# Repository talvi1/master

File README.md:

<h3>Road Roughness Measurement System</h3> 
<h4>Introduction</h4>
Road roughness data is expensive and painstaking to gather. A new approach minimizes the overall cost of such systems by building a low cost and modular system that can be used to take measurements of the road roughness and can be used to supplement the more expensive equipment to map all of the roadways. The system supports the measurement of road surface roughness where data is not currently being collected such as smaller rural municipalities roads and residential city roads. The measurement of road roughness along with images that provide visual reference are used to quantify road surface conditions. 

<h4>System Architecture</h4>

The system block diagram shows the architecture to capture, process and display the required. Three independent nodes are used to collect acceleration data from the road. Each node uses a 6-DoF MPU6050 accelerometer connected to a STM32 Cortex M3 microcontroller via I2C. The microcontroller processes the data and sends the data packets to a Xbee transmitter. The system operates in a star network topology using the IEEE 802.15.4 protocol to receive the frames from each node. The receiver is connected to the Raspberry Pi. The Raspberry Pi simultaneously receives position data from a GPS module and road images captured from the camera. The data is processed on the Raspberry Pi and sent to a server to be displayed on a website showing the worst quality roads on a map. 

<h4>Data Processing Pipeline</h4>

Raw acceleration data captured from the accelerometers needs to be processed in order to create a quantifiable measurment of road roughness. Accelerometer data is first passed through a DC blocking filter in order to remove the gravity bias from the measurements. A 10th order bandpass filter is used to remove noise from the measurments and data is then integrated to calculate velocity. An algorithm is then used to compute vertical displacement in m/m, which provides the required road roughness value.   

<h4>Image Processing Pipeline</h4>

Images are captured of the road surface in order to provide data regarding potholes and cracks in the road surface. 

Raw images are processed in order to provide an indication of the degradation of the road surface. The edge detection algorithm is used after passing the image through a gaussian blur filter. The edge is dilated and a convex hull algorithm is used to draw an approximate outline around the cracks or potholes in the road surface. The size of the convex polygon indicates the severity of the degradation in the road surface.    

<h4>Results</h4>

The data captured and processed from the system descibed above was display on a website to show the roughest parts of the roads in the city. 

<h6>Notes</h6>
<sup>See attached report and paper under the document folder to see further details regarding the software/hardware implementation, testing and challenges encountered.</sup>

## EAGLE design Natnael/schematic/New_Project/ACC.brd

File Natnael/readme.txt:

Natnael 

voltage regulator

https://www.digikey.ca/product-detail/en/PHR-2/455-1165-ND/608607/?itemSeq=284871182

https://www.digikey.ca/product-detail/en/B2B-PH-K-S(LF)(SN)/455-1704-ND/926611/?itemSeq=284871166

https://www.digikey.ca/product-detail/en/232/36-232-ND/303804/?itemSeq=284870675

https://www.digikey.ca/product-detail/en/EN22/N145-ND/704825/?itemSeq=284870583

https://www.ablic.com/en/doc/datasheet/voltage_regulator/S818_E.pdf

https://www.digikey.com/product-detail/en/ablic-u-s-a-inc/S-818A33AUC-BGNT2U/1662-2000-1-ND/6696434

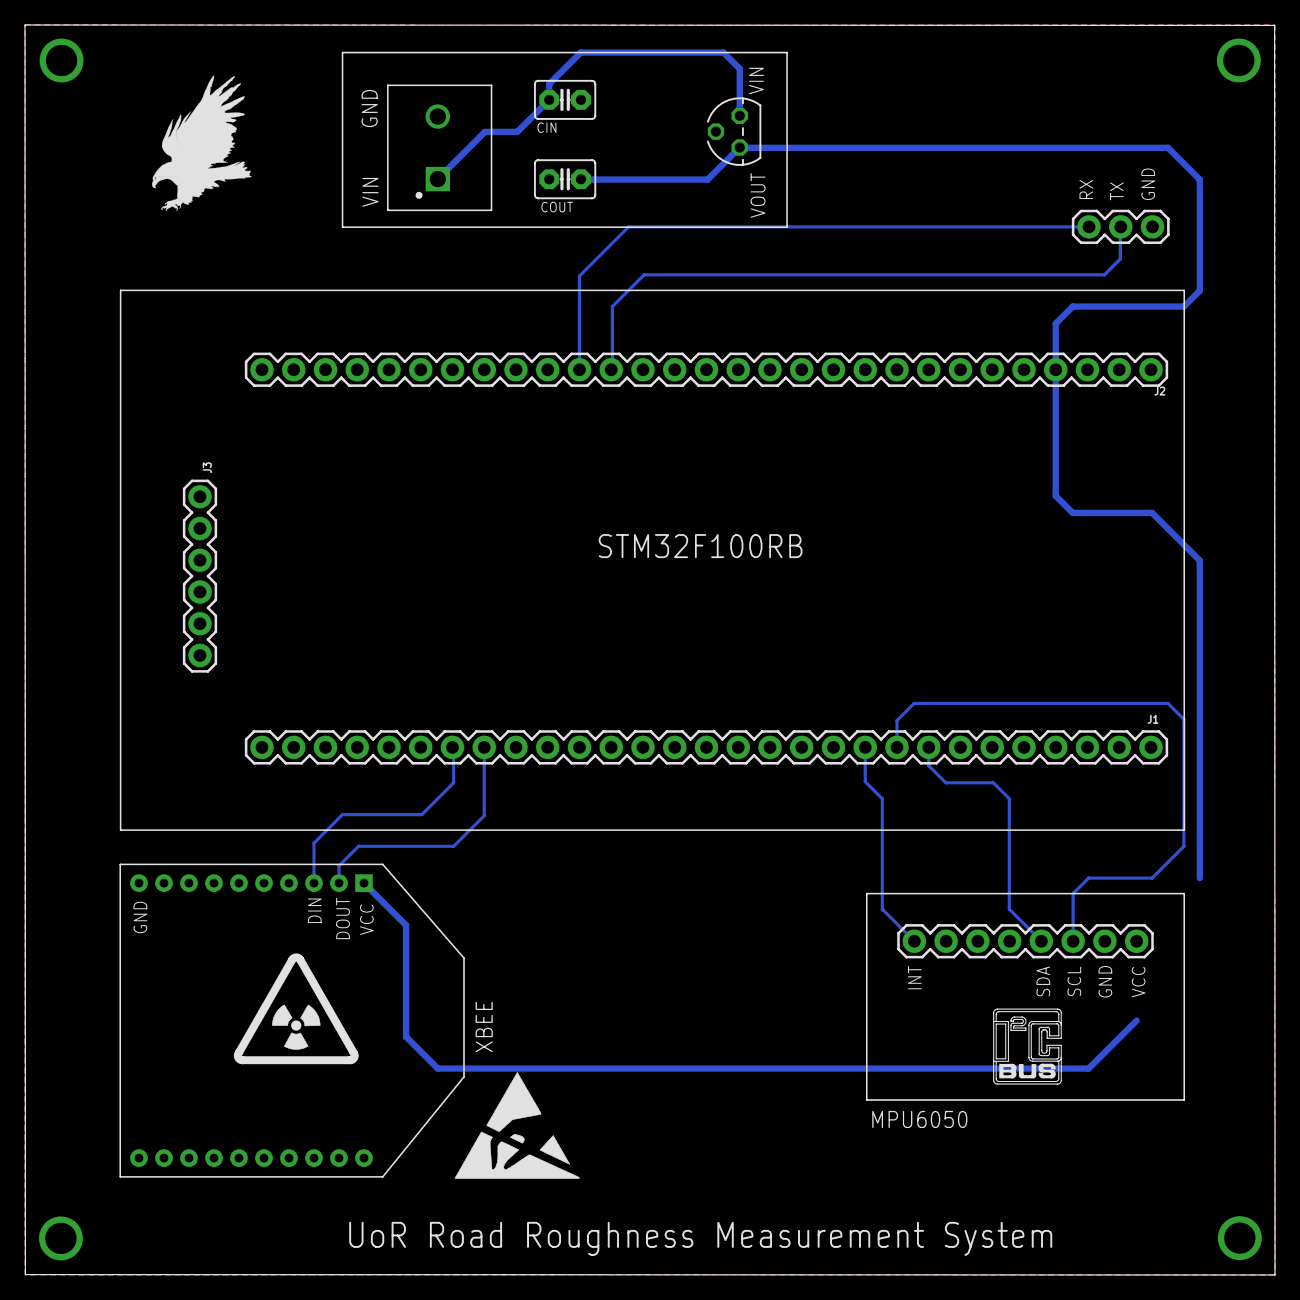
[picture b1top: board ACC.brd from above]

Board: 2 copper layers, 100.0 x 100.0 mm, 14 parts (0 on the bottom side), 10 nets.

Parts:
CIN: 1uF; C2.5-3
COUT: 2.2uF; C2.5-3
J1, J2: 1X29
J3: 1X06
J4: 1935161; PHOENIX_1935161
J5: 1X03
MPU6050: 1X08
U$2: EAGLE-PLC-8MM
U$3: ESD_10.00
U$5: I2C
U$6: RADIOACTIVE_10.00
VOLTAGE_REGULATOR: LP2950Z; TO92
XBEE: XBEE

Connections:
3V3: COUT.1, J2.4, VOLTAGE_REGULATOR.1
GND: CIN.2, COUT.2, J1.2, J1.29, J2.2, J2.29, J4.2, J5.1, MPU6050.7, VOLTAGE_REGULATOR.2, XBEE.10
PA2: J2.18, J5.2
PA3: J2.19, J5.3
PA9: J1.23, XBEE.3
PA10: J1.22, XBEE.2
PB5: J1.10, MPU6050.1
PB6: J1.9, MPU6050.6
PB7: J1.8, MPU6050.5
VIN: CIN.1, J4.1, VOLTAGE_REGULATOR.3

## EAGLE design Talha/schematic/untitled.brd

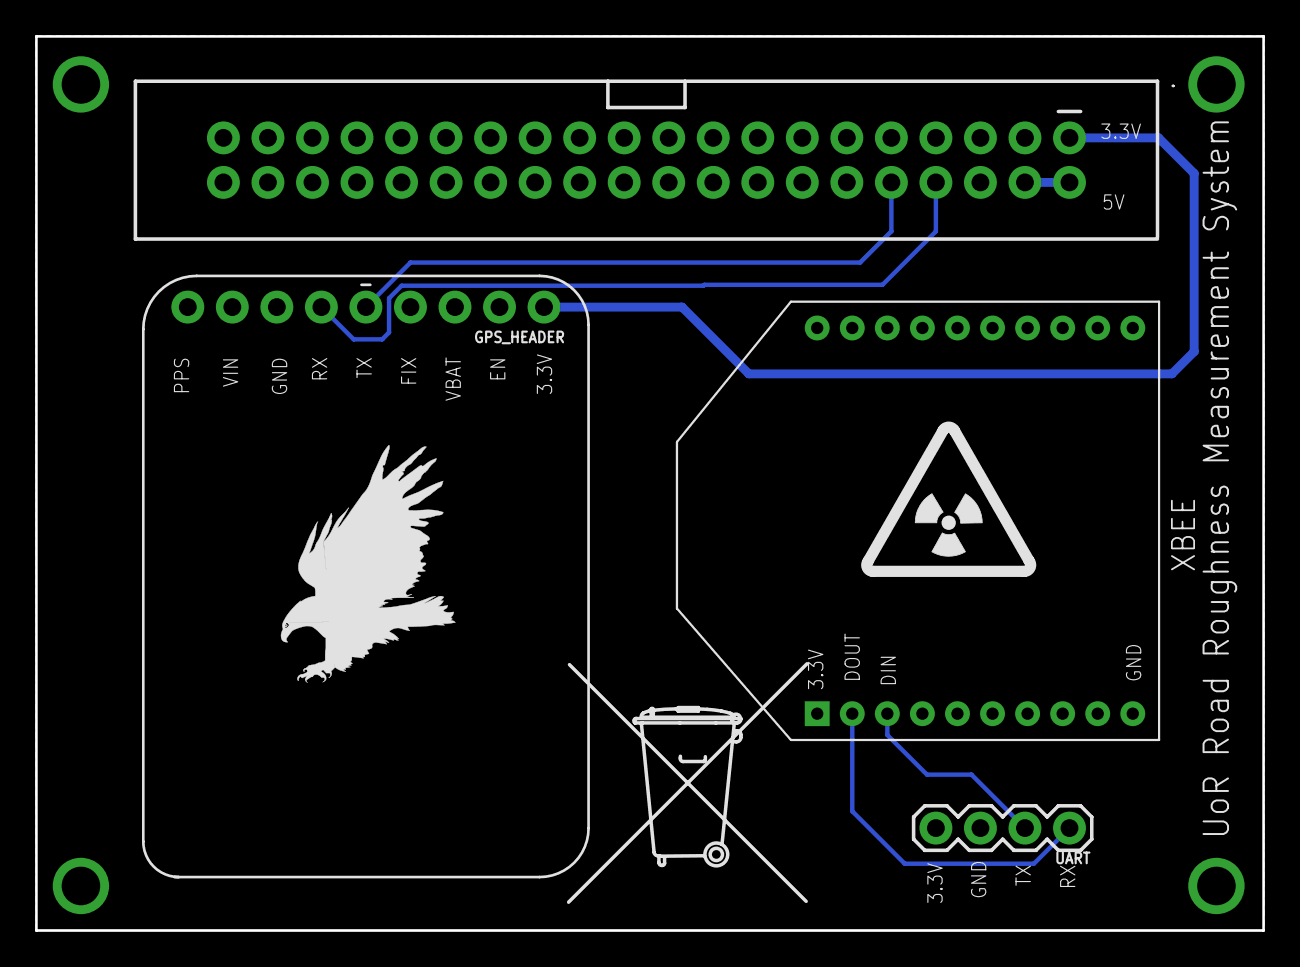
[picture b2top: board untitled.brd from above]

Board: 2 copper layers, 70.0 x 51.0 mm, 7 parts (0 on the bottom side), 8 nets.

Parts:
.: RASPBERRYPI-40-PIN-GPIO_PTH; 2X20_SHROUDED
GPS_HEADER: 1X09_NO_SILK
U$3: EAGLE-PLC-10MM
U$4: RADIOACTIVE_10.00
U$5: TONNE
UART: 1X04
XBEE: XBEE

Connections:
5V: ..2, ..4
GND: ..6, ..9, ..14, ..20, ..25, ..30, ..34, ..39, GPS_HEADER.7, UART.3, XBEE.10
unnamed: ..1, GPS_HEADER.1
unnamed: ..10, GPS_HEADER.5
unnamed: ..8, GPS_HEADER.6
RX: UART.1, XBEE.2
TX: UART.2, XBEE.3
VCC: ..17, XBEE.1

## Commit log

2018-09-24 test
2018-09-24 casdasdasd
2018-09-24 folder created
2018-11-29 test tala
2018-11-29 ACc and ADC test 1
2018-11-29 read me created
2018-11-29 read me for project
2018-12-02 initiall web push
2018-12-12 SPI example code
2019-01-10 updated acc driver
2019-01-11 testing for spi
2019-01-12 accelorometer test code
2019-01-12 more example code for stm32
2019-01-12 accel test code using i2c for mpu 6050
2019-01-13 accel test to produce float acceleration values
2019-01-13 initial push for raspberry pi code for camera, xbee, gps
2019-01-16 inital code push
2019-01-16 documentation for project device added
2019-01-20 i2c update
2019-01-20 readme file for natnael
2019-01-20 logs update
2019-01-20 logs removed
2019-01-20 logs re-added
2019-01-20 read me update
2019-01-20 python document created
2019-01-20 read me update 2
2019-01-21 updated regusters for MPU6050
2019-01-21 serial output formated for live plot
2019-01-23 Reference academic papers added & python csv code
2019-01-25 added reference paper on data processing
2019-01-25 Logs upload
2019-01-26 log 2
2019-01-26 added matlab scripts for filters and plotting data
2019-01-26 filter codes
2019-01-27 added testing plan
2019-01-28 xbee communication updated
2019-01-28 readme created
2019-01-30 update matlab scripts for filtering
2019-01-30 Updated testing plan
2019-01-31 testing plan updated and another reference paper added
2019-02-02 integration code for raspberry pi
2019-02-02 Battery/ Voltage regulator
2019-02-03 image processing script
2019-02-08 timer threads for camera
2019-02-08 xbee full code
2019-02-08 new xbee code
2019-02-15 threads working and putting data in queues
2019-02-16 fix for threading issues
2019-02-18 acc integration test
2019-02-18 updated voltage regulator
2019-02-18 pcb schematic created
2019-02-18 accelerometer with interrupt working
2019-02-19 formatting of accelerometer data to work with xbee frames
2019-02-20 working xbee transfer
2019-02-20 writing data received from xbee in csv format
2019-02-21 schematic
2019-02-22 pcb update
2019-02-22 pcb another update\
2019-02-22 updatae on pcb
2019-02-22 pcb design update
2019-02-22 testing plan updated
2019-02-23 pcb gerber files generated
2019-02-28 parsing collected data file
2019-02-28 parsed file to get acceleration data
2019-03-02 saving parsed data to file
2019-03-02 logs for multiple data collection
2019-03-03 config update
2019-03-04 Testing gps, camera, accel in car, with data logs collected
2019-03-06 fixed code to process raw data to be stored as csv file
2019-03-09 additional gps, xbee, camera integration code
2019-03-09 database upload
2019-03-09 filter implementation for accelerometer data and changes to data processing/collection
2019-03-10 logged data with image and gps
2019-03-10 multi processing data collection working, file parsing working
2019-03-10 real time collection and processing code added
2019-03-11 fix for reading uneven lengths of data from devices
2019-03-12 upload to database: update
2019-03-12 functions added to integrate acceleration data
2019-03-13 realtime plot
2019-03-13 php upload
2019-03-13 added real time plot functionality to accelerometer data
2019-03-14 real time graph of data fixed to be more real time
2019-03-15 fix for reading uneven number of frames from different xbee devices
2019-03-16 loading images from database to websites
2019-03-16 data recorded from bump testing and additional code for processing data
2019-03-16 updated display
2019-03-17 data from testing parsed, different filters (FIR, IIR) implemented
2019-03-17 implemented pothole recognition using image processing and cleaned up code for real time data collection
2019-03-18 real time data upload to data base implemented
2019-03-19 plots from bump testing data added
2019-03-20 updating testing plan record
2019-03-22 demo and realtime upload with test images
2019-03-25 testing results and plotting videos
2019-03-25 test videos
2019-03-25 additional bump testing data logs, code documentation
2019-03-25 additional bump testing data logs and code documentation
2019-03-25 removed vid
2019-03-25 more code comments
2019-03-25 removed videos
2019-03-26 data base upload
2019-03-28 commenting codes
2019-03-29 updating block diagram
2019-04-05 powerpoint slides
2019-04-11 complete project folder update
2019-04-11 update-folder name
2019-04-11 Code added to main project folder with comments
2020-01-07 cleaned up file structure
2020-02-08 readme updated
2020-08-30 read me completed

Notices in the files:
parts and their libraries:
SparkFun-Connectors: Licensing: Creative Commons ShareAlike 4.0 International - https://creativecommons.org/licenses/by-sa/4.0
